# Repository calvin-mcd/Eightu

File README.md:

# Eightu

These are stagger & ortho pcbs for the Eightu by @obobobobo!
Eightu is a 13.25u 40% keyboard. It features an island spacebar with 8u spacebar support (and many different bottom row options), usbc daughterboard, arrow cluster, 7degree typing angle, tadpole mount, m4 screws and big bezels.

Please beware!!!
The staggered pcb has been fully tested and is working. 
The ortho version has not been fully tested. 

## Layout

- Stagger

[Link](http://www.keyboard-layout-editor.com/#/gists/97695b20dd87207f9ccde1adff4b1bca)

- Ortho

[Link](http://www.keyboard-layout-editor.com/#/gists/30d9483fe7658ad6d1901818d84a543f)

## Pictures

(renders are not up to date regarding Keylayouts, refer to KLEs above)

## Disclaimer

This PCB has been fully tested and is confirmed to work. However, no-one involved in this project is responsible for any usage issues that may arise. Order at your own risk. Feel free to edit, modify and otherwise utilise these files.

## License

Shield: 

This work is licensed under a  
[Creative Commons Attribution-NonCommercial-ShareAlike 4.0 International License](http://creativecommons.org/licenses/by-nc-sa/4.0/).

## Credits

Any questions, contact Calvin0563 on Discord.

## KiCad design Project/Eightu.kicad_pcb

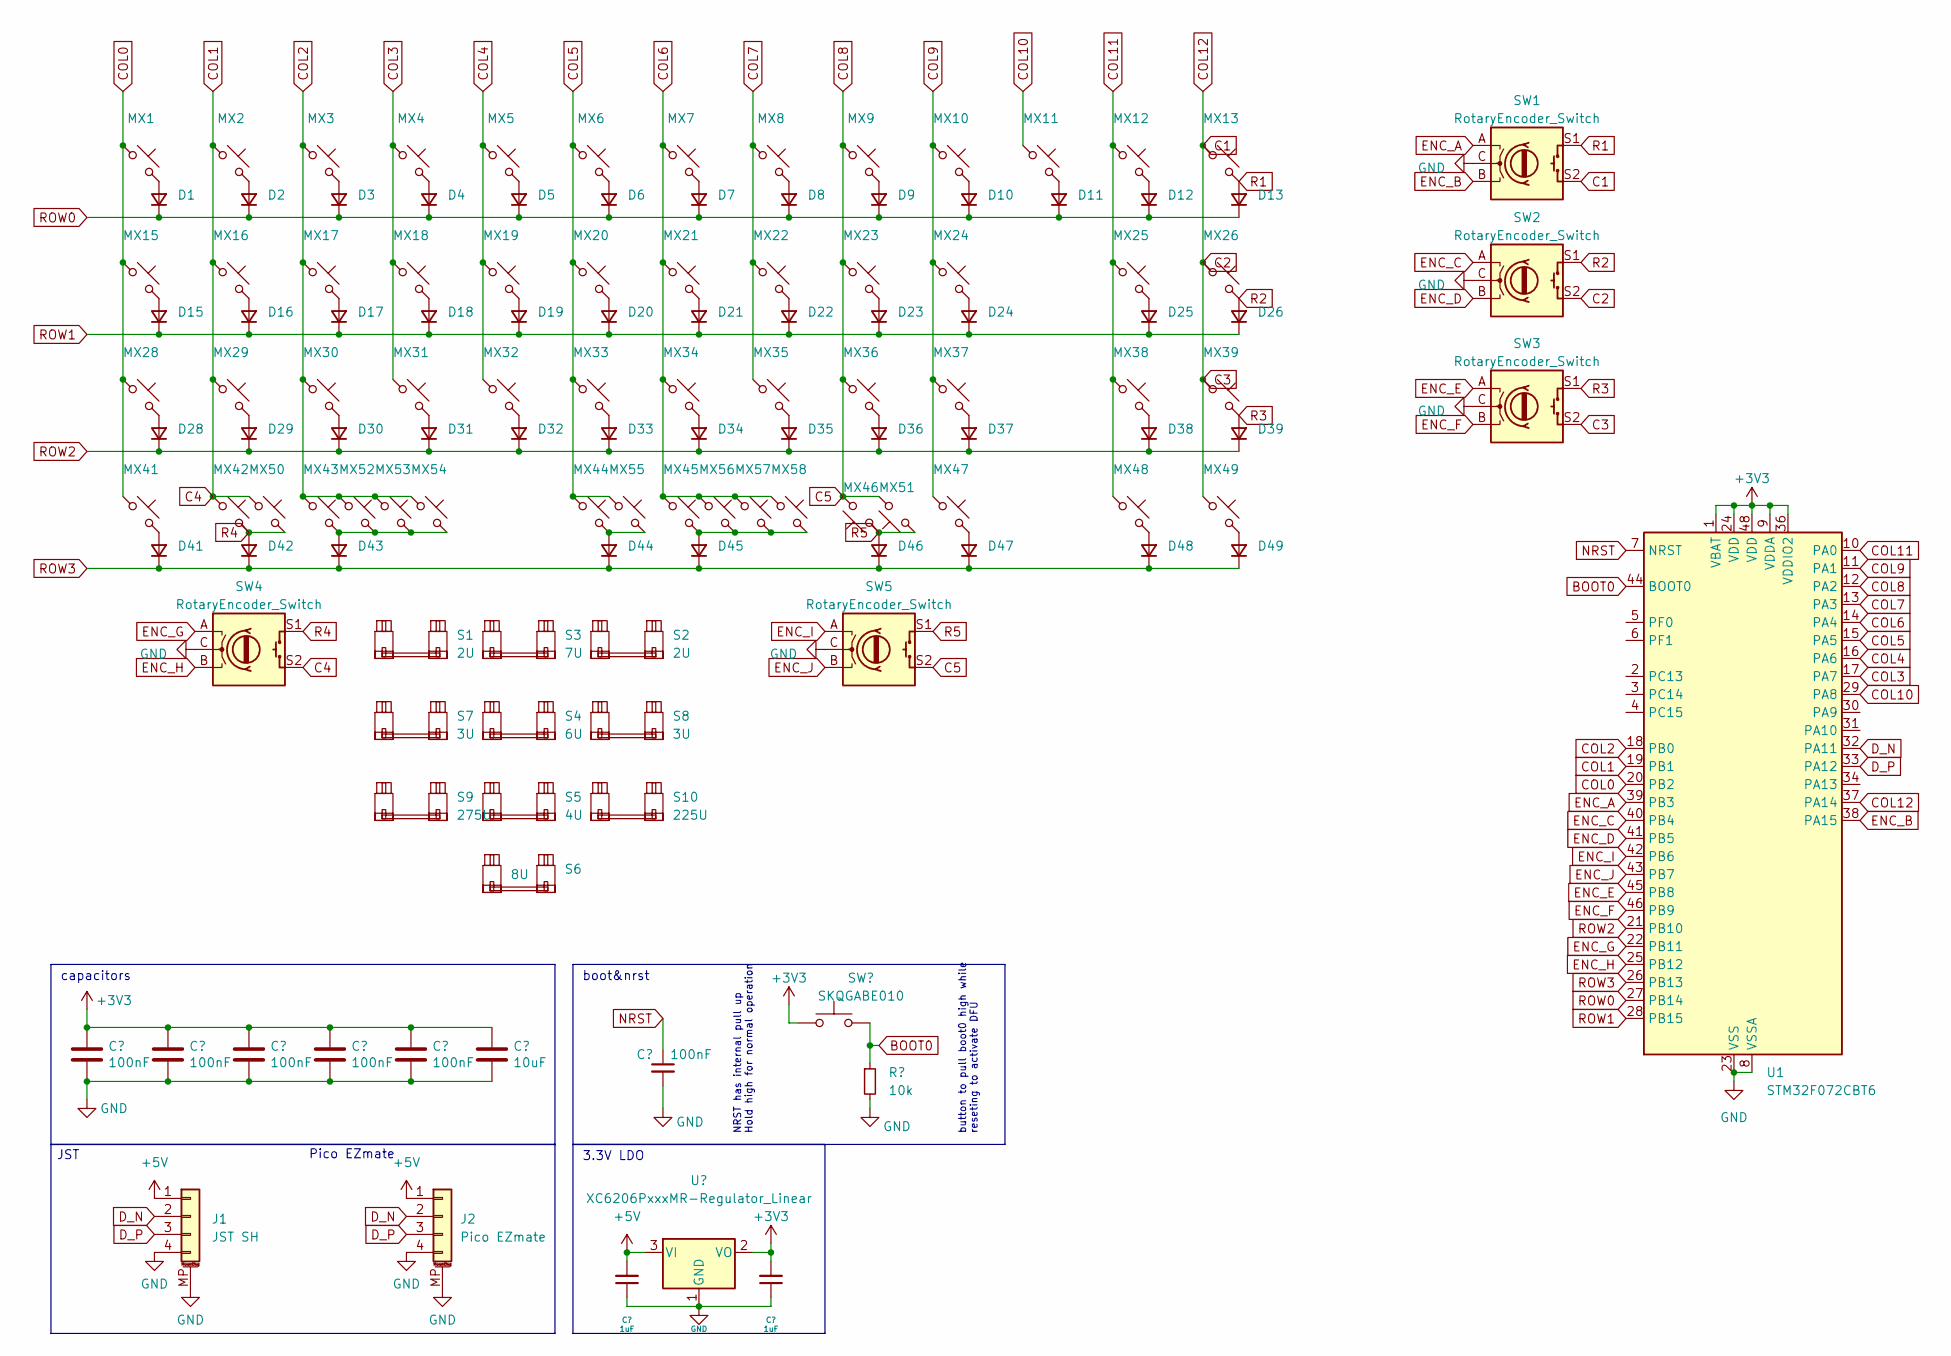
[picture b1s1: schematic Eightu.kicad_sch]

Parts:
C1, C2, C3, C4, C5, C7: 100nF; C_0402_1005Metric; LCSC C307331
C6: 10uF; C_0603_1608Metric
C8, C9: 1uF; C_0402_1005Metric; LCSC C52923
D1, D2, D3, D4, D5, D6, D7, D8, D9, D10, D11, D12, D13, D15, D16, D17, D18, D19, D20, D21, D22, D23, D24, D25, D26, D28, D29, D30, D31, D32, D33, D34, D35, D36, D37, D38, D39, D41, D42, D43, D44, D45, D46, D47, D48, D49: D_Small; D_SOD-123F
J1: JST SH; JST_SH_SM04B-SRSS-TB_1x04-1MP_P1.00mm_Horizontal
J2: Pico EZmate; Molex_Pico-EZmate_78171-0004_1x04-1MP_P1.20mm_Vertical
MX1, MX2, MX3, MX4, MX5, MX6, MX7, MX8, MX9, MX10, MX11, MX12, MX13, MX16, MX17, MX18, MX19, MX20, MX21, MX22, MX23, MX24, MX26, MX29, MX30, MX31, MX32, MX33, MX34, MX35, MX36, MX37, MX38, MX39, MX43, MX44, MX45, MX47, MX48, MX49, MX50, MX51, MX52, MX53, MX54, MX55, MX56, MX57, MX58: MX_SW_solder; SW_MX_1u
MX15: MX_SW_solder; SW_MX_1.25u
MX25, MX28: MX_SW_solder; SW_MX_1.75u
MX41, MX42, MX46: MX_SW_solder; SW_MX_1.5u
R1: 10k; R_0402_1005Metric
S1, S2: 2U; STAB_MX_P_2u
S3: 7U; STAB_MX_P_7u
S4: 6U; STAB_MX_P_6u
S5: 4U; STAB_MX_P_4u
S6: 8U; STAB_MX_P_8u
S7, S8: 3U; STAB_MX_P_3u
S9: 275U; STAB_MX_P_2.75u
S10: 225U; STAB_MX_P_2.25u
SW1, SW2, SW3, SW4, SW5: RotaryEncoder_Switch; ROT_Alps_EC11E-Switch
SW6: SKQGABE010; SW_SPST_SKQG_WithStem; LCSC C115351
U1: STM32F072CBT6; LQFP-48_7x7mm_P0.5mm; JlcRotOffset 90
U2: XC6206PxxxMR-Regulator_Linear; SOT-23; LCSC C5446

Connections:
+3V3: C1.1, C2.1, C3.1, C4.1, C5.1, C6.1, C9.2, SW6.1, U1.1 (VBAT), U1.9 (VDDA), U1.24 (VDD), U1.36 (VDDIO2), U1.48 (VDD), U2.2 (VO)
+5V: C8.2, J1.1, J2.1, U2.3 (VI)
BOOT0: R1.1, SW6.2, U1.44 (BOOT0)
C1: MX13.1, MX26.1, MX39.1, MX49.1, SW1.S2, SW2.S2, SW3.S2, U1.37 (PA14)
C4: MX2.1, MX16.1, MX29.1, MX42.1, MX50.1, SW4.S2, U1.19 (PB1)
C5: MX9.1, MX23.1, MX36.1, MX46.2, MX51.2, SW5.S2, U1.12 (PA2)
COL0: MX1.1, MX15.1, MX28.1, MX41.1, U1.20 (PB2)
COL2: MX3.1, MX17.1, MX30.1, MX43.1, MX52.1, MX53.1, MX54.1, U1.18 (PB0)
COL3: MX4.1, MX18.1, MX31.1, U1.17 (PA7)
COL4: MX5.1, MX19.1, MX32.1, U1.16 (PA6)
COL5: MX6.1, MX20.1, MX33.1, MX44.1, MX55.1, U1.15 (PA5)
COL6: MX7.1, MX21.1, MX34.1, MX45.1, MX56.1, MX57.1, MX58.1, U1.14 (PA4)
COL7: MX8.1, MX22.1, MX35.1, U1.13 (PA3)
COL9: MX10.1, MX24.1, MX37.1, MX47.1, U1.11 (PA1)
COL10: MX11.1, U1.29 (PA8)
COL11: MX12.1, MX25.1, MX38.1, MX48.1, U1.10 (PA0)
D_N: J1.2, J2.2, U1.32 (PA11)
D_P: J1.3, J2.3, U1.33 (PA12)
ENC_A: SW1.A, U1.39 (PB3)
ENC_B: SW1.B, U1.38 (PA15)
ENC_C: SW2.A, U1.40 (PB4)
ENC_D: SW2.B, U1.41 (PB5)
ENC_E: SW3.A, U1.45 (PB8)
ENC_F: SW3.B, U1.46 (PB9)
ENC_G: SW4.A, U1.22 (PB11)
ENC_H: SW4.B, U1.25 (PB12)
ENC_I: SW5.A, U1.42 (PB6)
ENC_J: SW5.B, U1.43 (PB7)
GND: C1.2, C2.2, C3.2, C4.2, C5.2, C6.2, C7.2, C8.1, C9.1, J1.4, J1.MP (MountPin), J2.4, J2.MP (MountPin), R1.2, SW1.C, SW2.C, SW3.C, SW4.C, SW5.C, U1.8 (VSSA), U1.23 (VSS), U1.35 (VSS), U1.47 (VSS), U2.1 (GND)
NRST: C7.1, U1.7 (NRST)
unnamed: D1.2 (A), MX1.2
unnamed: D2.2 (A), MX2.2
unnamed: D3.2 (A), MX3.2
unnamed: D4.2 (A), MX4.2
unnamed: D5.2 (A), MX5.2
unnamed: D6.2 (A), MX6.2
unnamed: D7.2 (A), MX7.2
unnamed: D8.2 (A), MX8.2
unnamed: D9.2 (A), MX9.2
unnamed: D10.2 (A), MX10.2
unnamed: D11.2 (A), MX11.2
unnamed: D12.2 (A), MX12.2
unnamed: D15.2 (A), MX15.2
unnamed: D16.2 (A), MX16.2
unnamed: D17.2 (A), MX17.2
unnamed: D18.2 (A), MX18.2
unnamed: D19.2 (A), MX19.2
unnamed: D20.2 (A), MX20.2
unnamed: D21.2 (A), MX21.2
unnamed: D22.2 (A), MX22.2
unnamed: D23.2 (A), MX23.2
unnamed: D24.2 (A), MX24.2
unnamed: D25.2 (A), MX25.2
unnamed: D28.2 (A), MX28.2
unnamed: D29.2 (A), MX29.2
unnamed: D30.2 (A), MX30.2
unnamed: D31.2 (A), MX31.2
unnamed: D32.2 (A), MX32.2
unnamed: D33.2 (A), MX33.2
unnamed: D34.2 (A), MX34.2
unnamed: D35.2 (A), MX35.2
unnamed: D36.2 (A), MX36.2
unnamed: D37.2 (A), MX37.2
unnamed: D38.2 (A), MX38.2
unnamed: D41.2 (A), MX41.2
unnamed: D43.2 (A), MX43.2, MX52.2, MX53.2, MX54.2
unnamed: D44.2 (A), MX44.2, MX55.2
unnamed: D45.2 (A), MX45.2, MX56.2, MX57.2, MX58.2
unnamed: D47.2 (A), MX47.2
unnamed: D48.2 (A), MX48.2
unnamed: D49.2 (A), MX49.2
R1: D13.2 (A), MX13.2, SW1.S1
R2: D26.2 (A), MX26.2, SW2.S1
R3: D39.2 (A), MX39.2, SW3.S1
R4: D42.2 (A), MX42.2, MX50.2, SW4.S1
R5: D46.2 (A), MX46.1, MX51.1, SW5.S1
ROW0: D1.1 (K), D2.1 (K), D3.1 (K), D4.1 (K), D5.1 (K), D6.1 (K), D7.1 (K), D8.1 (K), D9.1 (K), D10.1 (K), D11.1 (K), D12.1 (K), D13.1 (K), U1.27 (PB14)
ROW1: D15.1 (K), D16.1 (K), D17.1 (K), D18.1 (K), D19.1 (K), D20.1 (K), D21.1 (K), D22.1 (K), D23.1 (K), D24.1 (K), D25.1 (K), D26.1 (K), U1.28 (PB15)
ROW2: D28.1 (K), D29.1 (K), D30.1 (K), D31.1 (K), D32.1 (K), D33.1 (K), D34.1 (K), D35.1 (K), D36.1 (K), D37.1 (K), D38.1 (K), D39.1 (K), U1.21 (PB10)
ROW3: D41.1 (K), D42.1 (K), D43.1 (K), D44.1 (K), D45.1 (K), D46.1 (K), D47.1 (K), D48.1 (K), D49.1 (K), U1.26 (PB13)

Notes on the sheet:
JST
Pico EZmate
NRST has internal pull up Hold high for normal operation
3.3V LDO
capacitors
button to pull boot0 high while reseting to activate DFU
boot&nrst

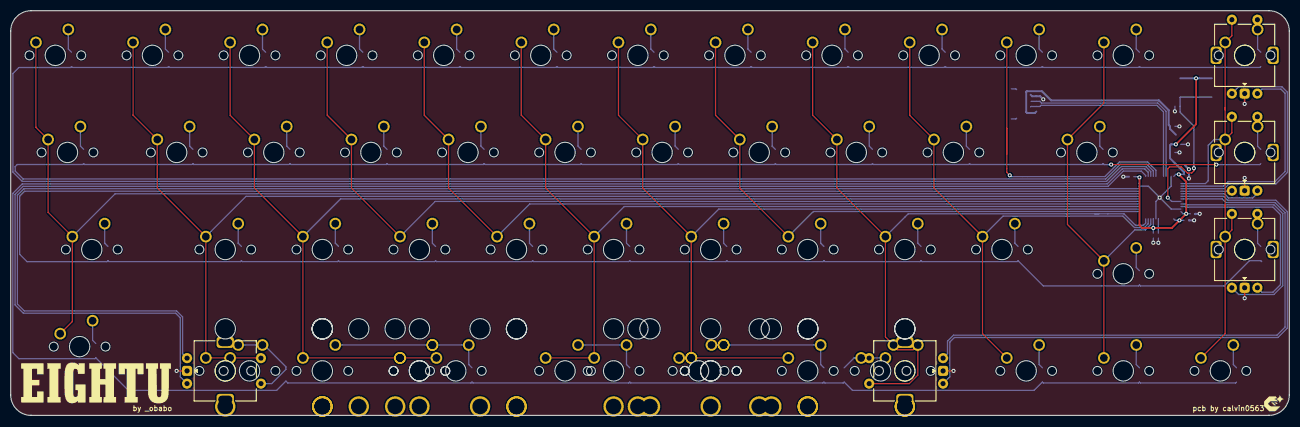
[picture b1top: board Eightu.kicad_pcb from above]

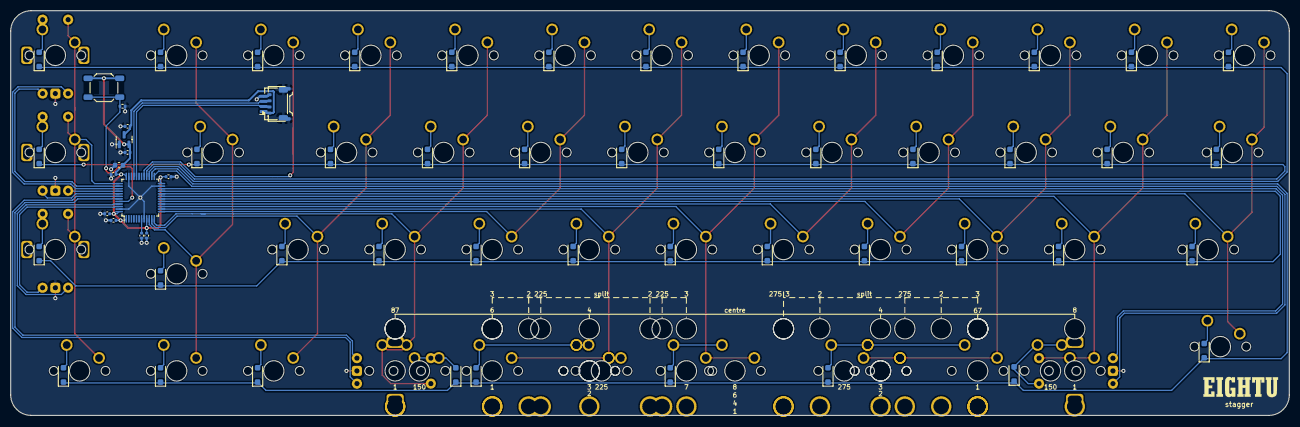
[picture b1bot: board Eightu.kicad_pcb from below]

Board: 2 copper layers, 250.9 x 79.4 mm, 131 parts (61 on the bottom side), 80 nets.

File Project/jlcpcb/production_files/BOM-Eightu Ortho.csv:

Comment,Designator,Footprint,LCSC
SKQGABE010,SW6,SW_SPST_SKQG_WithStem,C115351
10k,R1,R_0402_1005Metric,C25744
100nF,"C1,C2,C3,C4,C5,C7",C_0402_1005Metric,C307331
1uF,"C8,C9",C_0402_1005Metric,C52923
XC6206PxxxMR-Regulator_Linear,U2,SOT-23,C5446
Pico EZmate,J2,Molex_Pico-EZmate_78171-0004_1x04-1MP_P1.20mm_Vertical,C588524
D_Small,"D1,D10,D11,D12,D13,D14,D15,D16,D17,D18,D19,D2,D20,D21,D22,D23,D24,D25,D26,D27,D28,D29,D3,D30,D31,D32,D33,D34,D35,D36,D37,D38,D39,D4,D40,D41,D42,D43,D44,D45,D46,D47,D48,D49,D5,D50,D52,D6,D7,D8,D9",D_SOD-123F,C81598
STM32F072CBT6,U1,LQFP-48_7x7mm_P0.5mm,C81720
10uF,C6,C_0603_1608Metric,C96446

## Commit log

2023-11-27 initialise project
2023-11-27 cleaned up project folder
2023-12-02 backup
2024-04-13 firmware
2024-04-21 firmware update
2024-10-14 fresh ortho gerbers
2024-10-14 update gerbers
